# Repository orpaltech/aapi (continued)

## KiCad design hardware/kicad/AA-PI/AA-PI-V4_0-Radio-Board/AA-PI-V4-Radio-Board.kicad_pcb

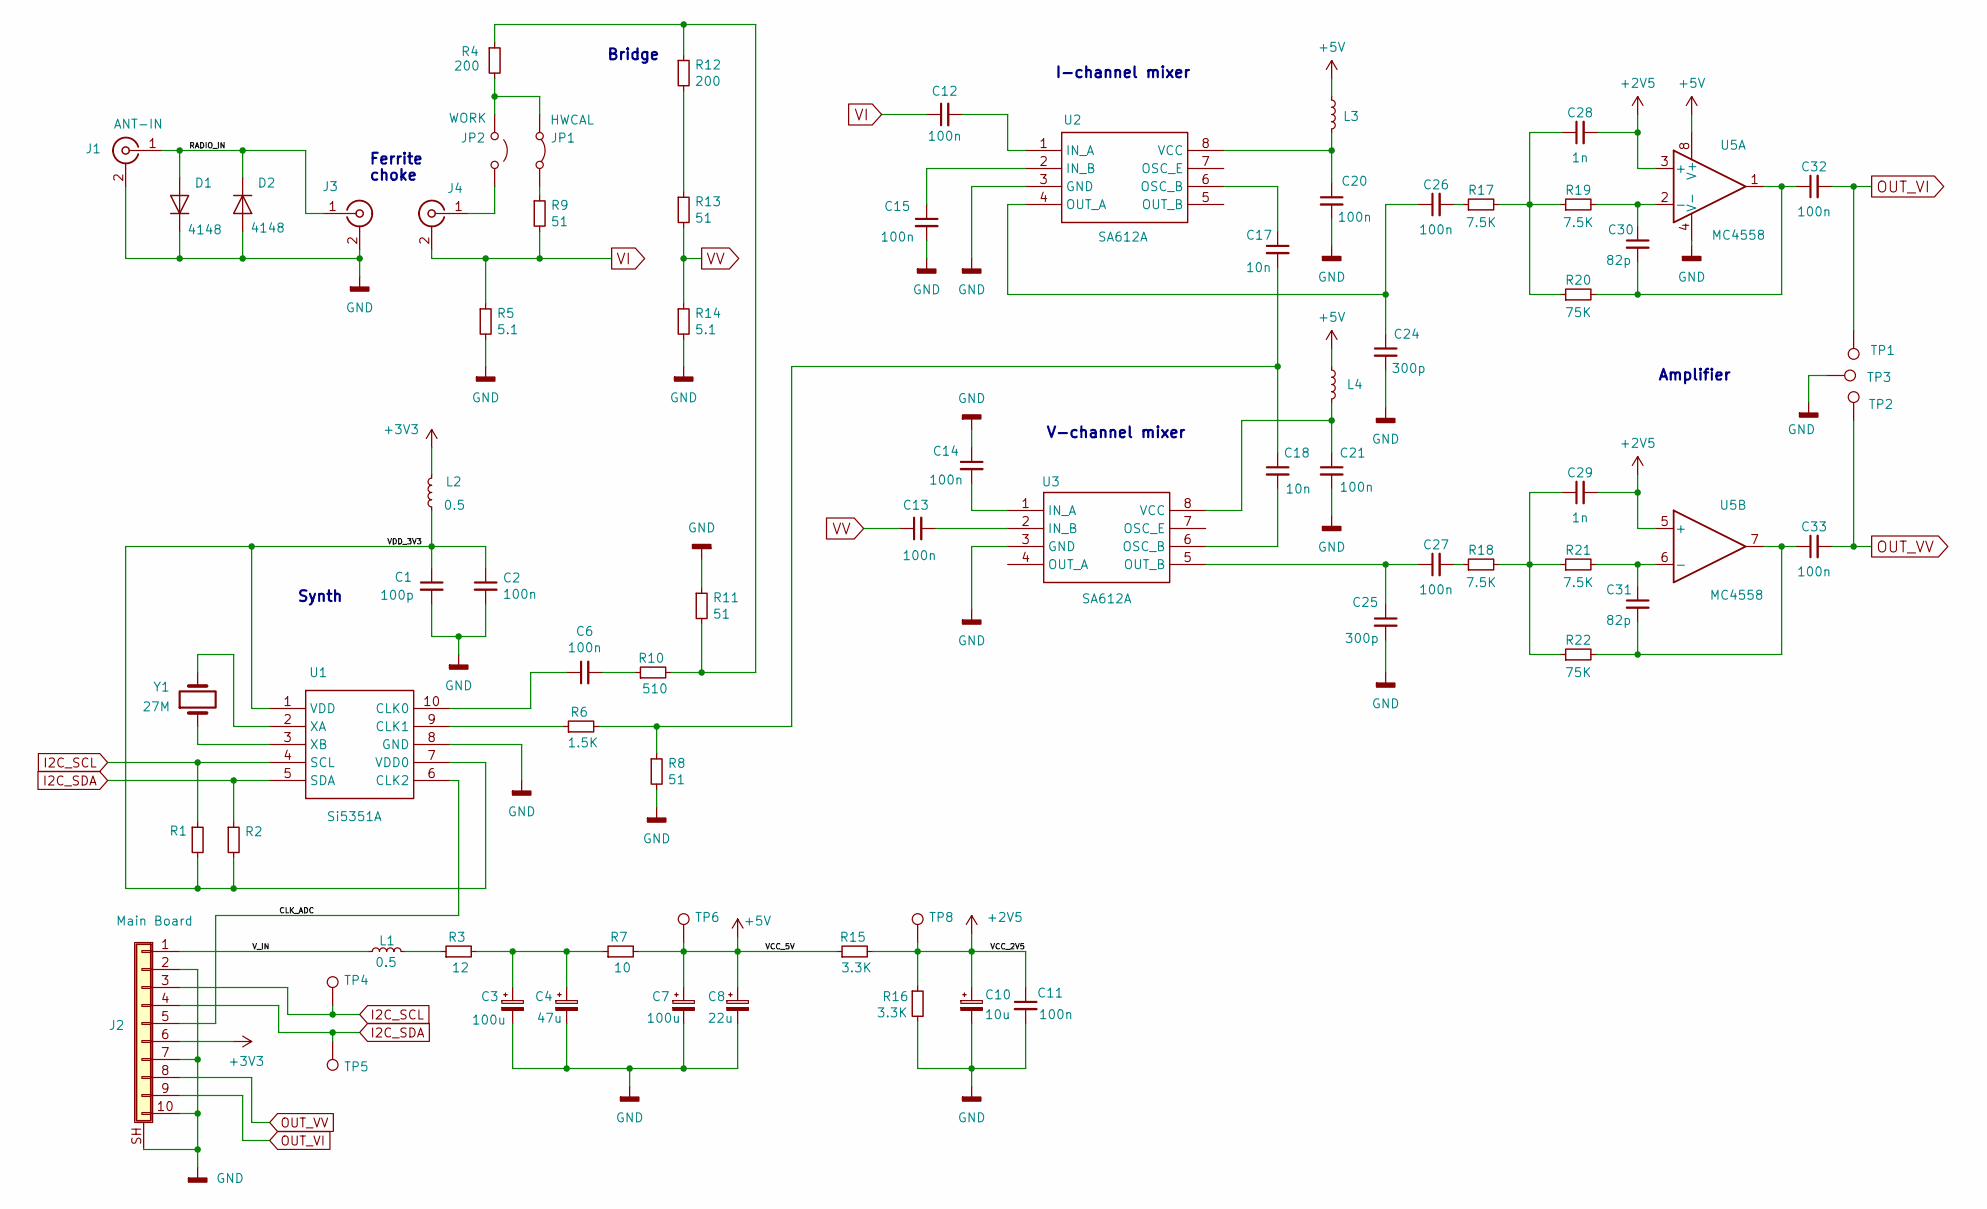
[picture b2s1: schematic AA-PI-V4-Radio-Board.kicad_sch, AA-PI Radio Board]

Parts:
C1: 100p; C_0805_2012Metric_Pad1.15x1.40mm_HandSolder
C2, C6, C11, C12, C13, C14, C15, C20, C21, C26, C27, C32, C33: 100n; C_0805_2012Metric_Pad1.15x1.40mm_HandSolder
C3, C7: 100u; CP_EIA-7343-31_Kemet-D
C4: 47u; CP_EIA-3528-21_Kemet-B
C8: 22u; CP_EIA-3528-21_Kemet-B
C10: 10u; CP_EIA-3528-21_Kemet-B
C17, C18: 10n; C_0805_2012Metric_Pad1.15x1.40mm_HandSolder
C24, C25: 300p; C_0805_2012Metric_Pad1.15x1.40mm_HandSolder
C28, C29: 1n; C_0805_2012Metric_Pad1.15x1.40mm_HandSolder
C30, C31: 82p; C_0805_2012Metric_Pad1.15x1.40mm_HandSolder
D1, D2: 4148; D_SOD-323_HandSoldering
J1: ANT-IN; SMA_Amphenol_901-144_Vertical
J2: Main Board; 1.25-AB-SMT-10pin-Vertical
J3, J4: INDUCT; MMCX_Molex_73415-1471_Vertical
JP1: HWCAL; PinHeader_1x02_P2.00mm_Vertical
JP2: WORK; PinHeader_1x02_P2.00mm_Vertical
L1, L2, L3, L4: 0.5; L_0805_2012Metric_Pad1.15x1.40mm_HandSolder
R1, R2: 10K; R_0805_2012Metric_Pad1.15x1.40mm_HandSolder
R3: 12; R_0805_2012Metric_Pad1.15x1.40mm_HandSolder
R4, R12: 200; R_0805_2012Metric_Pad1.15x1.40mm_HandSolder
R5, R14: 5.1; R_0805_2012Metric_Pad1.15x1.40mm_HandSolder
R6: 1.5K; R_0805_2012Metric_Pad1.15x1.40mm_HandSolder
R7: 10; R_0805_2012Metric_Pad1.15x1.40mm_HandSolder
R8, R9, R11, R13: 51; R_0805_2012Metric_Pad1.15x1.40mm_HandSolder
R10: 510; R_0805_2012Metric_Pad1.15x1.40mm_HandSolder
R15, R16: 3.3K; R_0805_2012Metric_Pad1.15x1.40mm_HandSolder
R17, R18, R19, R21: 7.5K; R_0805_2012Metric_Pad1.15x1.40mm_HandSolder
R20, R22: 75K; R_0805_2012Metric_Pad1.15x1.40mm_HandSolder
TP1, TP2, TP3, TP4, TP5, TP6, TP8: TestPoint; TestPoint_THTPad_D1.0mm_Drill0.5mm
U1: Si5351A; SOP50P490X110-10N; Manufacturer_Part_Number Si5351A-B-GT
U2, U3: SA612A; SOIC127P600X175-8N; Manufacturer_Part_Number SA612A
U5: MC4558; SOIC127P600X175-8N
Y1: 27M; Crystal_SMD_5032-2Pin_5.0x3.2mm

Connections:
+2V5: C10.1, C11.1, C28.2, C29.2, R15.2, R16.1, TP8.1, U5.3 (+), U5.5 (+)
+3V3: J2.6, L2.1
+5V: C7.1, C8.1, L3.1, L4.1, R7.2, R15.1, TP6.1, U5.8 (V+); also elsewhere on the board
/CLK_ADC: J2.5, U1.6 (CLK2)
/RADIO_IN: D1.2 (A), D2.1 (K), J1.1 (In), J3.1 (In)
/VDD_3V3: C1.1, C2.1, L2.2, R1.2, R2.2, U1.1 (VDD), U1.7 (VDD0)
/V_IN: J2.1, L1.1
GND: C1.2, C2.2, C3.2, C4.2, C7.2, C8.2, C10.2, C11.2, C14.1, C15.2, C20.2, C21.2, C24.2, C25.2, D1.1 (K), D2.2 (A), J1.2 (Ext), J2.2, J2.7, J2.10, J2.SH (Shield), J3.2 (Ext), R5.2, R8.2, R11.1, R14.2, R16.2, TP3.1, U1.8 (GND), U2.3 (GND), U3.3 (GND), U5.4 (V-); also elsewhere on the board
I2C_SCL: J2.3, R1.1, TP4.1, U1.4 (SCL)
I2C_SDA: J2.4, R2.1, TP5.1, U1.5 (SDA)
unnamed 10: C3.1, C4.1, R3.2, R7.1; also elsewhere on the board
unnamed: C6.2, R10.1
unnamed: C17.2, C18.1, R6.2, R8.1
unnamed: C26.2, R17.1
unnamed: C27.2, R18.1
unnamed: C28.1, R17.2, R19.1, R20.1
unnamed: C29.1, R18.2, R21.1, R22.1
unnamed: C30.2, C32.1, R20.2, U5.1
unnamed: C31.2, C33.1, R22.2, U5.7
unnamed: J4.1 (In), JP2.2 (B)
unnamed: JP1.1 (A), JP2.1 (A), R4.2
unnamed: JP1.2 (B), R9.1
unnamed: L1.2, R3.1
unnamed: R4.1, R10.2, R11.2, R12.1
unnamed: R12.2, R13.1
unnamed: C6.1, U1.10 (CLK0)
unnamed: R6.1, U1.9 (CLK1)
unnamed: U1.2 (XA), Y1.2
unnamed: U1.3 (XB), Y1.1
unnamed: C12.2, U2.1 (IN_A)
unnamed: C15.1, U2.2 (IN_B)
unnamed: C17.1, U2.6 (OSC_B)
unnamed: C24.1, C26.1, U2.4 (OUT_A)
unnamed: C20.1, L3.2, U2.8 (VCC)
unnamed: C14.2, U3.1 (IN_A)
unnamed: C13.2, U3.2 (IN_B)
unnamed: C18.2, U3.6 (OSC_B)
unnamed: C25.1, C27.1, U3.5 (OUT_B)
unnamed: C21.1, L4.2, U3.8 (VCC)
unnamed: C30.1, R19.2, U5.2 (-)
unnamed: C31.1, R21.2, U5.6 (-)
OUT_VI: C32.2, J2.9, TP1.1
OUT_VV: C33.2, J2.8, TP2.1
VI: C12.1, J4.2 (Ext), R5.1, R9.2
VV: C13.1, R13.2, R14.1

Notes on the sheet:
Ferrite
choke
V-channel mixer
Amplifier
Synth
I-channel mixer
Bridge

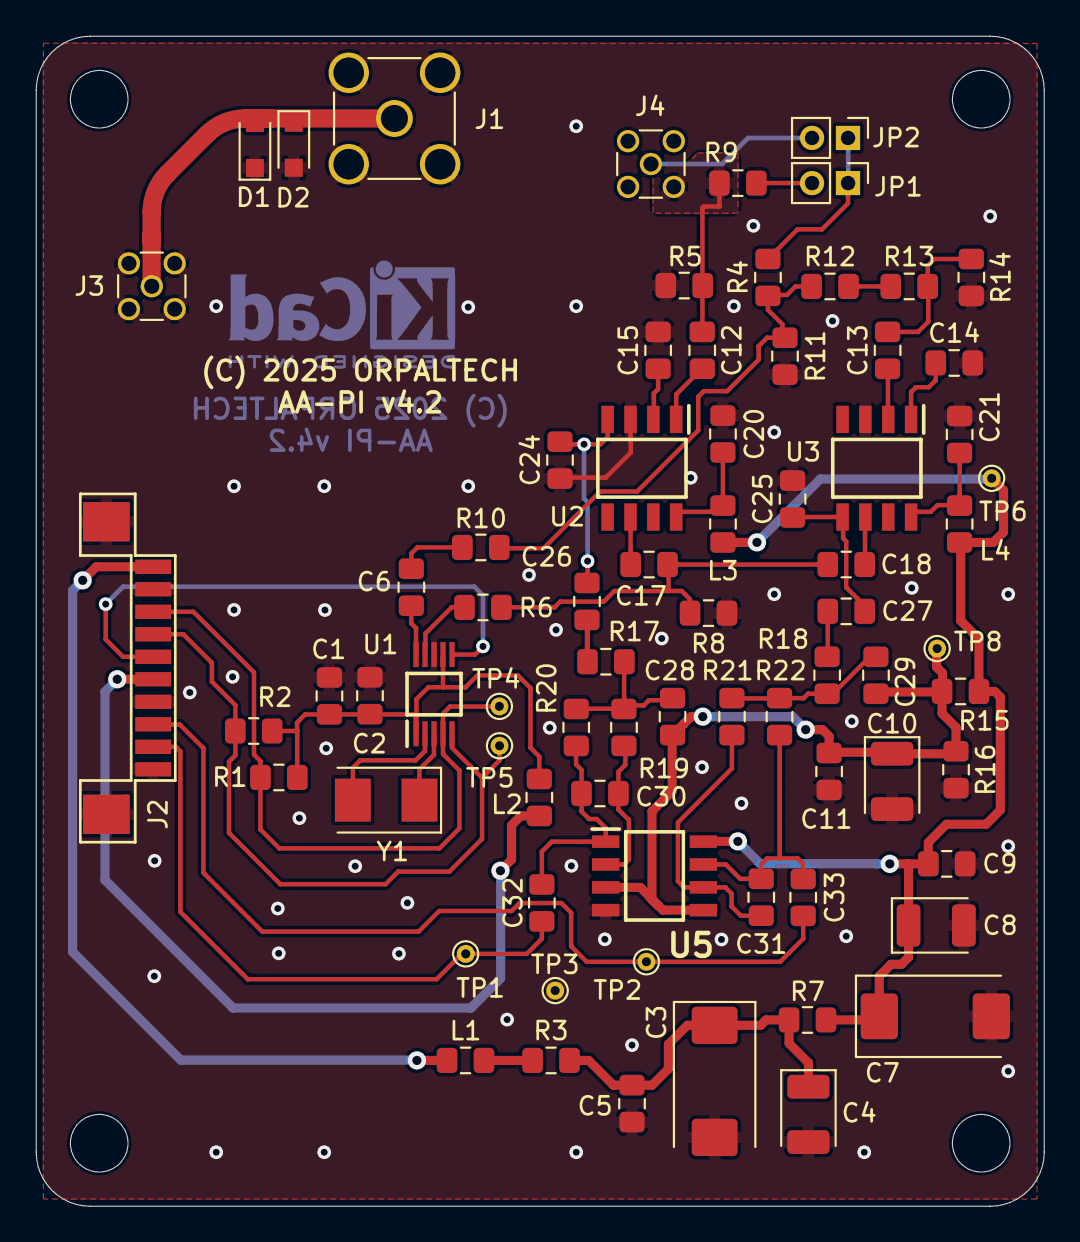
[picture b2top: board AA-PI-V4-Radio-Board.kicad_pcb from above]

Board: 2 copper layers, 56.0 x 65.0 mm, 79 parts (0 on the bottom side), 45 nets.

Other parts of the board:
C5, C9: 100n; C_0805_2012Metric_Pad1.15x1.40mm_HandSolder
MH1, MH2, MH3, MH4: MountingHole_3.2mm_M3_DIN965

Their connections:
+5V: C9.1; also elsewhere on the board
GND: C5.2, C9.2; also elsewhere on the board
unnamed 10: C5.1; also elsewhere on the board

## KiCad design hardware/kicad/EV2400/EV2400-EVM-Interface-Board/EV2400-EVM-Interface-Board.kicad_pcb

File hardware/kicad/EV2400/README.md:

This is my implementation of the Texas Instruments EV2400 Interface board. The board datasheet is located here http://www.ti.com/lit/ug/sluu446c/sluu446c.pdf

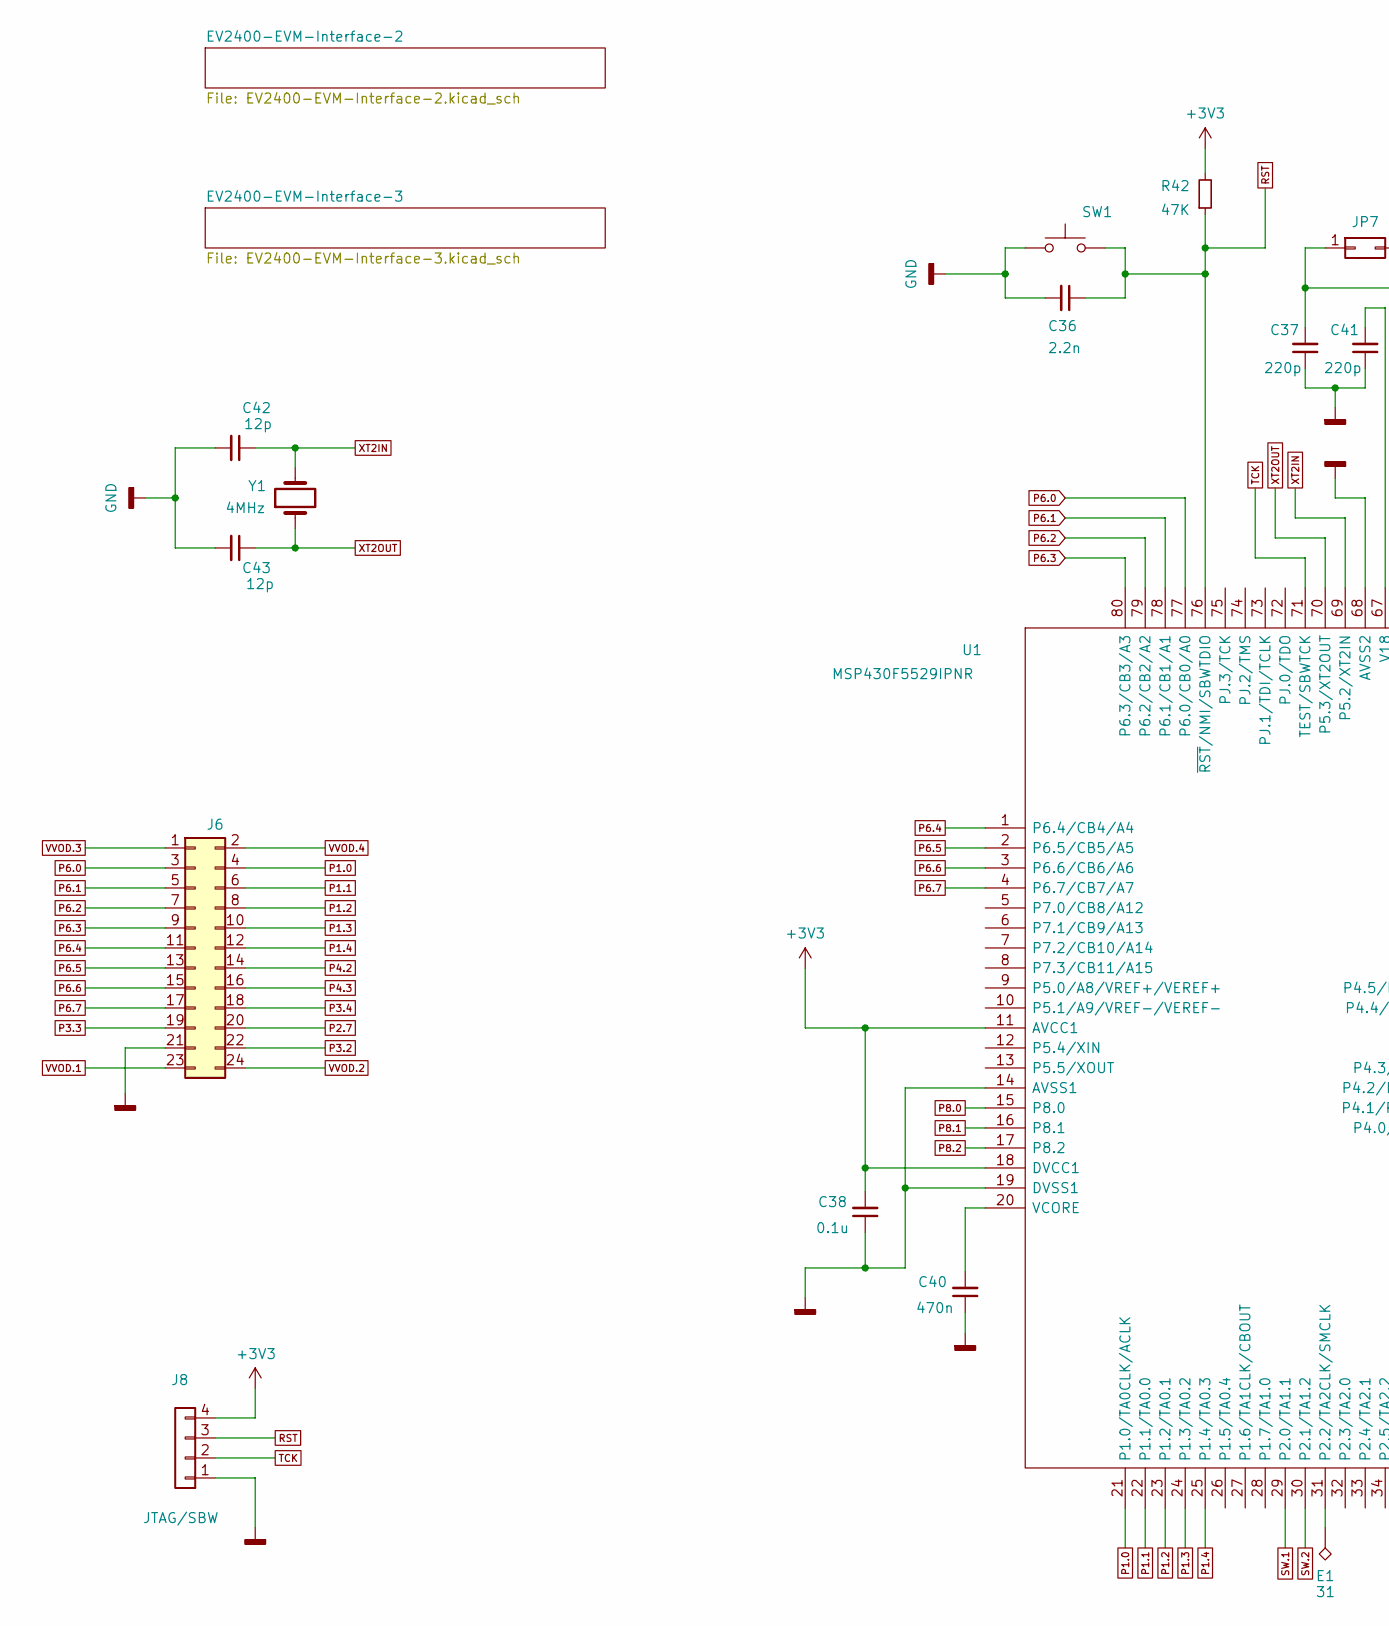
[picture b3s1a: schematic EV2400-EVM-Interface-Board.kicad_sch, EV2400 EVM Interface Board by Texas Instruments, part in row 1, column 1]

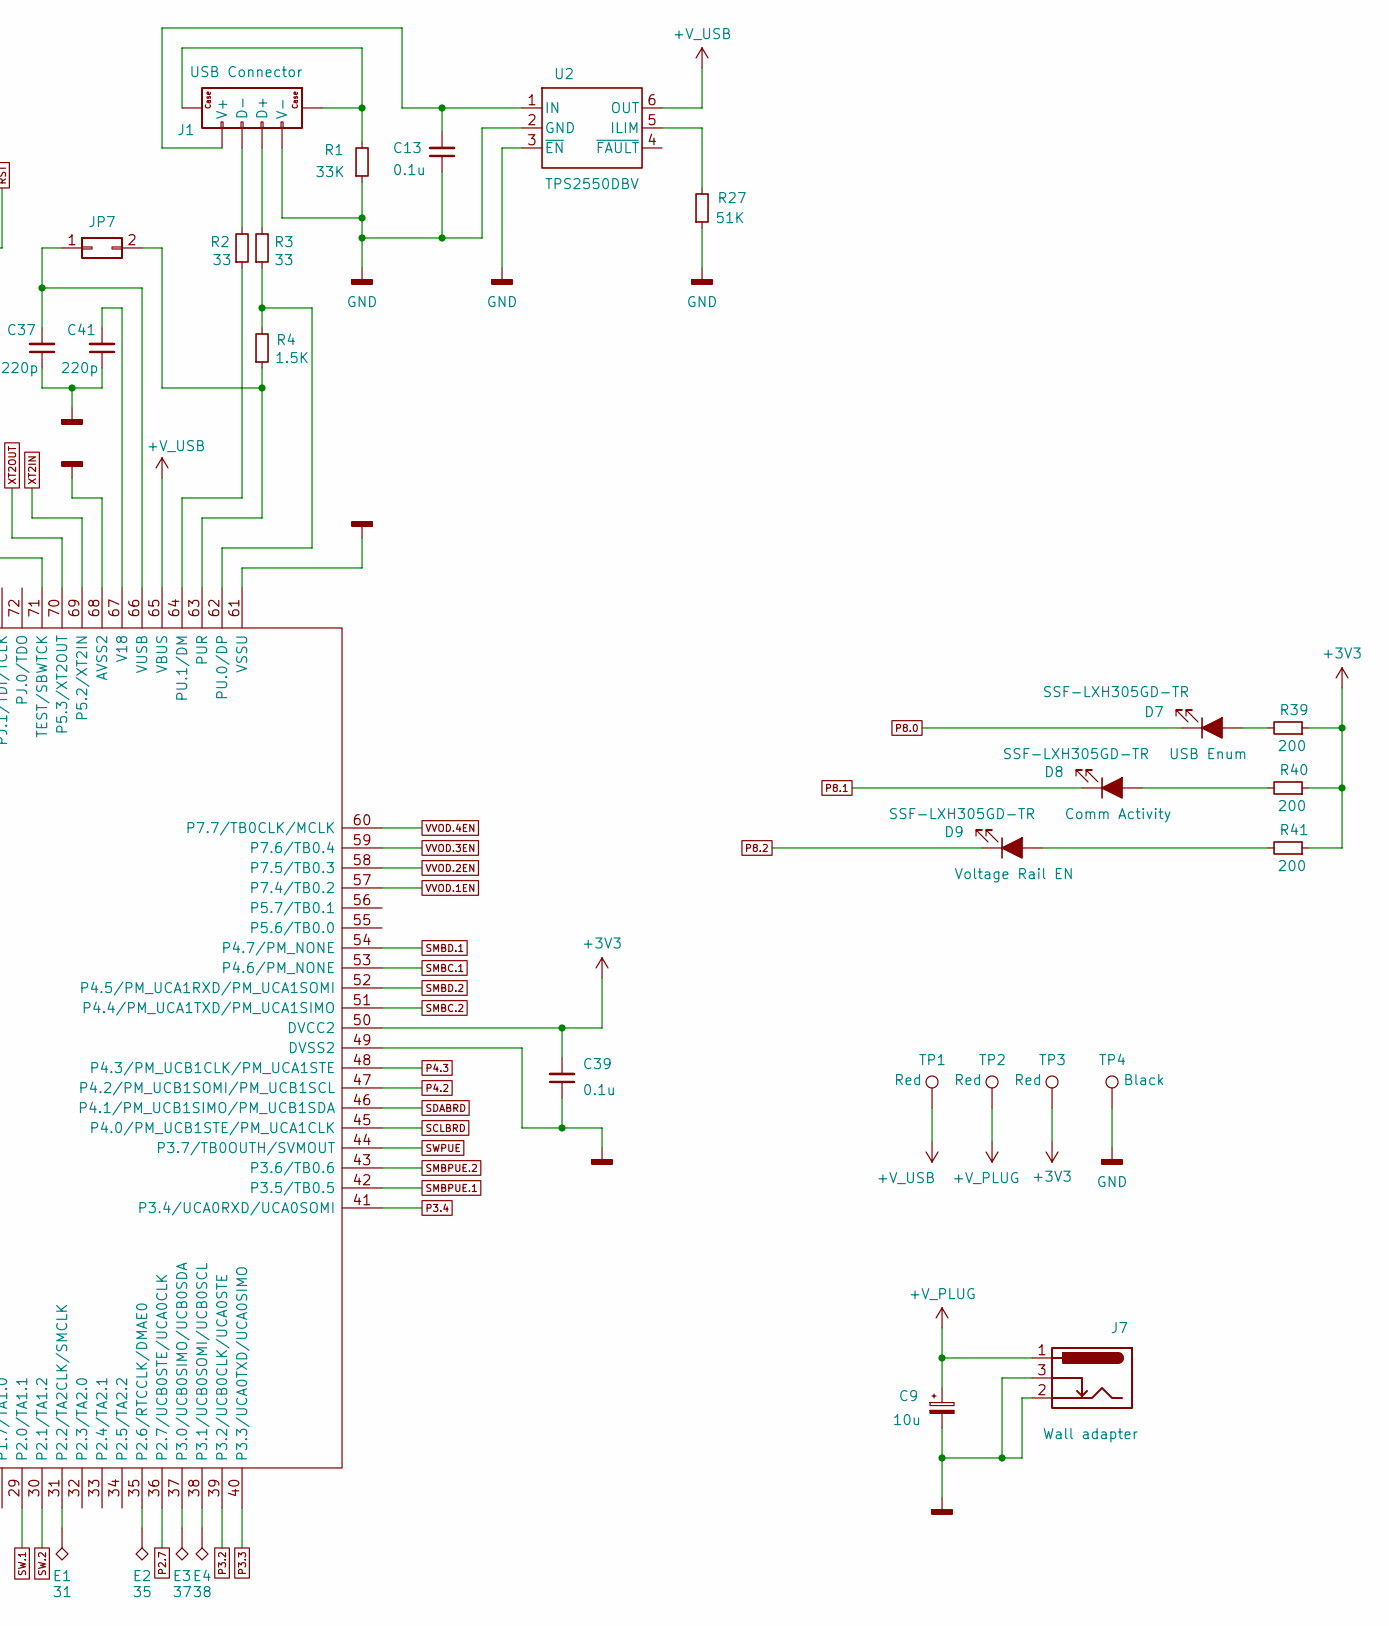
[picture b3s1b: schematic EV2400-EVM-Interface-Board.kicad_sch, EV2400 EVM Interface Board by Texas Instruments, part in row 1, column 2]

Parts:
C9: 10u; CP_EIA-3216-18_Kemet-A
C13, C38, C39: 0.1u; C_0603_1608Metric
C36: 2.2n; C_0603_1608Metric
C37, C41: 220p; C_0603_1608Metric
C40: 470n; C_0603_1608Metric
C42, C43: 12p; C_0603_1608Metric
D7, D8, D9: SSF-LXH305GD-TR; SSFLXH305GDTR
E1: 31; TestPoint_Pad_1.5x1.5mm
E2: 35; TestPoint_Pad_1.5x1.5mm
E3: 37; TestPoint_Pad_1.5x1.5mm
E4: 38; TestPoint_Pad_1.5x1.5mm
J1: USB Connector; USB_B_OST_USB-B1HSxx_Horizontal
J6: Conn_02x12_Odd_Even; PinHeader_2x12_P2.54mm_Horizontal
J7: Wall adapter; DC-050-SMD-Power-Jack
J8: JTAG/SBW; Molex_KK-254_AE-6410-04A_1x04_P2.54mm_Vertical
JP7: Conn_02x01; PinHeader_1x02_P2.54mm_Vertical
R1: 33K; R_0603_1608Metric
R2, R3: 33; R_0603_1608Metric
R4: 1.5K; R_0603_1608Metric
R27: 51K; R_0603_1608Metric
R39, R40, R41: 200; R_0603_1608Metric
R42: 47K; R_0603_1608Metric
SW1: EVQPSD02K
TP1, TP2, TP3, TP4: TestPoint; TestPoint_THTPad_D2.0mm_Drill1.0mm
U1: MSP430F5529IPNR; QFP50P1400X1400X160-80N; Manufacturer_Part_Number MSP430F5529IPNR
U2: TPS2550DBV; SOT95P280X145-6N; Manufacturer_Part_Number TPS2550DBV
Y1: 4MHz; Crystal_SMD_HC49-SD

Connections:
+3V3: C38.2, C39.2, J8.4, R39.1, R40.1, R41.1, R42.2, TP3.1, U1.11 (AVCC1), U1.18 (DVCC1), U1.50 (DVCC2); also elsewhere on the board
+V_PLUG: C9.1, J7.1, TP2.1; also elsewhere on the board
+V_USB: TP1.1, U1.65 (VBUS), U2.6 (OUT); also elsewhere on the board
GND: C9.2, C13.1, C36.2, C37.1, C38.1, C39.1, C40.1, C41.1, C42.2, C43.2, J1.4 (V-), J6.21, J7.2, J7.3, J8.1, R1.1, R27.1, SW1.1, TP4.1, U1.14 (AVSS1), U1.19 (DVSS1), U1.49 (DVSS2), U1.61 (VSSU), U1.68 (AVSS2), U2.2 (GND), U2.3 (~EN); also elsewhere on the board
unnamed: D7.2 (A), R39.2
unnamed: D8.2 (A), R40.2
unnamed: D9.2 (A), R41.2
unnamed: J1.3 (D+), R3.2
unnamed: J1.2 (D-), R2.2
unnamed: J1.5, R1.2
unnamed: C13.2, J1.1 (V+), U2.1 (IN)
unnamed: C37.2, JP7.1, U1.66 (VUSB)
unnamed: JP7.2, R4.1, U1.63 (PUR)
unnamed: E1.1, U1.31 (P2.2/TA2CLK/SMCLK)
unnamed: E2.1, U1.35 (P2.6/RTCCLK/DMAE0)
unnamed: E3.1, U1.37 (P3.0/UCB0SIMO/UCB0SDA)
unnamed: E4.1, U1.38 (P3.1/UCB0SOMI/UCB0SCL)
unnamed: R3.1, R4.2, U1.62 (PU.0/DP)
unnamed: R2.1, U1.64 (PU.1/DM)
unnamed: C41.2, U1.67 (V18)
unnamed: C40.2, U1.20 (VCORE)
unnamed: R27.2, U2.5 (ILIM)
P1.0: J6.4, U1.21 (P1.0/TA0CLK/ACLK)
P1.1: J6.6, U1.22 (P1.1/TA0.0)
P1.2: J6.8, U1.23 (P1.2/TA0.1)
P1.3: J6.10, U1.24 (P1.3/TA0.2)
P1.4: J6.12, U1.25 (P1.4/TA0.3)
P2.7: J6.20, U1.36 (P2.7/UCB0STE/UCA0CLK)
P3.2: J6.22, U1.39 (P3.2/UCB0CLK/UCA0STE)
P3.3: J6.19, U1.40 (P3.3/UCA0TXD/UCA0SIMO)
P3.4: J6.18, U1.41 (P3.4/UCA0RXD/UCA0SOMI)
P4.2: J6.14, U1.47 (P4.2/PM_UCB1SOMI/PM_UCB1SCL)
P4.3: J6.16, U1.48 (P4.3/PM_UCB1CLK/PM_UCA1STE)
P6.0: J6.3, U1.77 (P6.0/CB0/A0)
P6.1: J6.5, U1.78 (P6.1/CB1/A1)
P6.2: J6.7, U1.79 (P6.2/CB2/A2)
P6.3: J6.9, U1.80 (P6.3/CB3/A3)
P6.4: J6.11, U1.1 (P6.4/CB4/A4)
P6.5: J6.13, U1.2 (P6.5/CB5/A5)
P6.6: J6.15, U1.3 (P6.6/CB6/A6)
P6.7: J6.17, U1.4 (P6.7/CB7/A7)
P8.0: D7.1 (K), U1.15 (P8.0)
P8.1: D8.1 (K), U1.16 (P8.1)
P8.2: D9.1 (K), U1.17 (P8.2)
RST: C36.1, J8.3, R42.1, SW1.2, U1.76 (~RST/NMI/SBWTDIO)
SCLBRD: U1.45 (P4.0/PM_UCB1STE/PM_UCA1CLK); also elsewhere on the board
SDABRD: U1.46 (P4.1/PM_UCB1SIMO/PM_UCB1SDA); also elsewhere on the board
SMBC.1: U1.53 (P4.6/PM_NONE); also elsewhere on the board
SMBC.2: U1.51 (P4.4/PM_UCA1TXD/PM_UCA1SIMO); also elsewhere on the board
SMBD.1: U1.54 (P4.7/PM_NONE); also elsewhere on the board
SMBD.2: U1.52 (P4.5/PM_UCA1RXD/PM_UCA1SOMI); also elsewhere on the board
SMBPUE.1: U1.42 (P3.5/TB0.5); also elsewhere on the board
SMBPUE.2: U1.43 (P3.6/TB0.6); also elsewhere on the board
SW.1: U1.29 (P2.0/TA1.1); also elsewhere on the board
SW.2: U1.30 (P2.1/TA1.2); also elsewhere on the board
SWPUE: U1.44 (P3.7/TB0OUTH/SVMOUT); also elsewhere on the board
TCK: J8.2, U1.71 (TEST/SBWTCK)
VVOD.1: J6.23; also elsewhere on the board
VVOD.1EN: U1.57 (P7.4/TB0.2); also elsewhere on the board
VVOD.2: J6.24; also elsewhere on the board
VVOD.2EN: U1.58 (P7.5/TB0.3); also elsewhere on the board
VVOD.3: J6.1; also elsewhere on the board
VVOD.3EN: U1.59 (P7.6/TB0.4); also elsewhere on the board
VVOD.4: J6.2; also elsewhere on the board
VVOD.4EN: U1.60 (P7.7/TB0CLK/MCLK); also elsewhere on the board
XT2IN: C42.1, U1.69 (P5.2/XT2IN), Y1.2
XT2OUT: C43.1, U1.70 (P5.3/XT2OUT), Y1.1

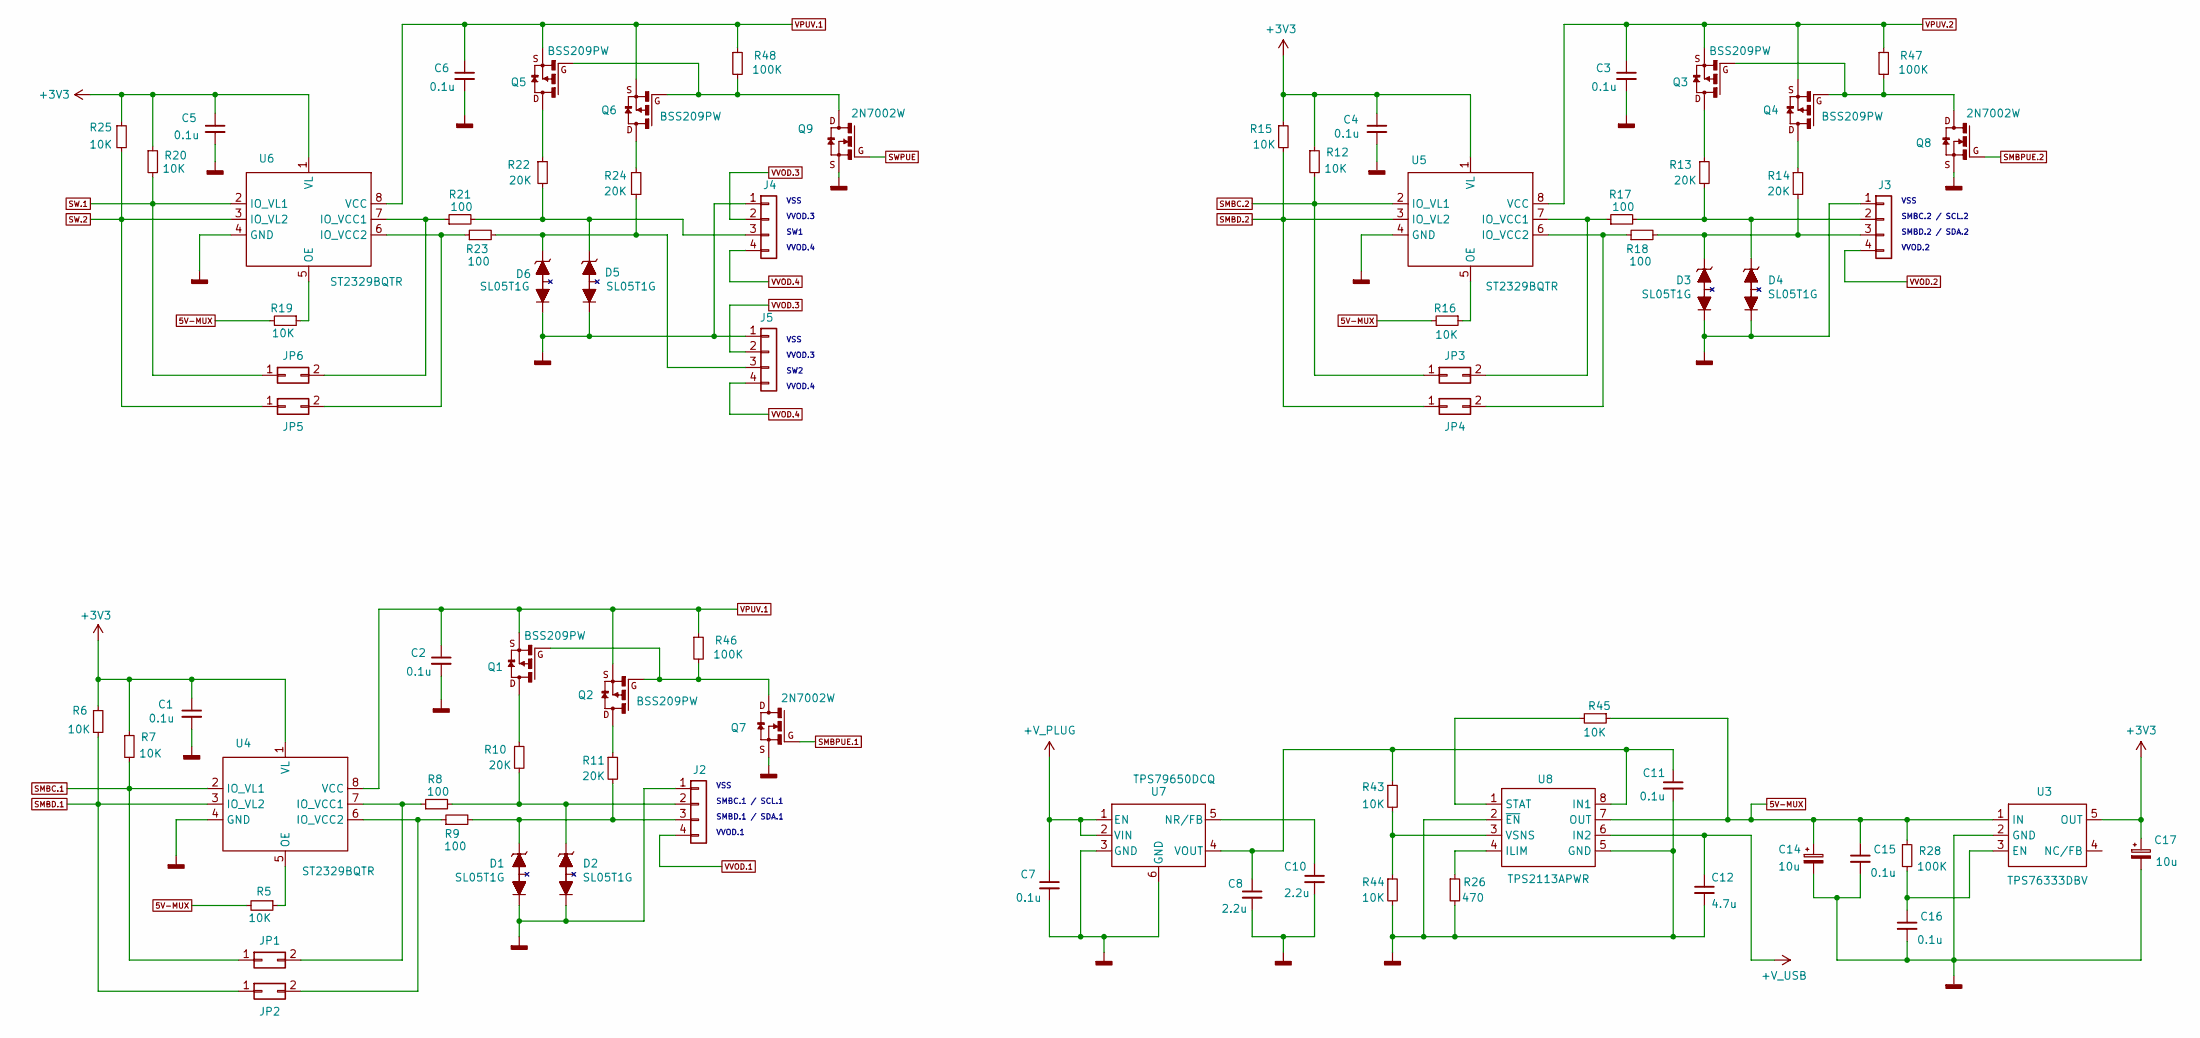
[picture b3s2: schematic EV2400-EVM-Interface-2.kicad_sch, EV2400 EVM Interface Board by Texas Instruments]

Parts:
C1, C2, C3, C4, C5, C6, C7, C11, C15, C16: 0.1u; C_0603_1608Metric
C8, C10: 2.2u; C_0805_2012Metric
C12: 4.7u; C_0805_2012Metric
C14, C17: 10u; CP_EIA-3216-18_Kemet-A
D1, D2, D3, D4, D5, D6: SL05T1G; SOT96P237X111-3N; Manufacturer_Part_Number SL05T1G
J2, J3, J4, J5: Conn_01x04; Molex_22053041
JP1, JP2, JP3, JP4, JP5, JP6: Conn_02x01; PinHeader_1x02_P2.54mm_Vertical
Q1, Q2, Q3, Q4, Q5, Q6: BSS209PW; SOT65P210X100-3N
Q7, Q8, Q9: 2N7002W; SOT65P220X100-3N
R5, R6, R7, R12, R15, R16, R19, R20, R25, R43, R44, R45: 10K; R_0603_1608Metric
R8, R9, R17, R18, R21, R23: 100; R_0603_1608Metric
R10, R11, R13, R14, R22, R24: 20K; R_0603_1608Metric
R26: 470; R_0603_1608Metric
R28, R46, R47, R48: 100K; R_0603_1608Metric
U3: TPS76333DBV; SOT95P280X145-5N; Manufacturer_Part_Number TPS76333DBVT
U4, U5, U6: ST2329BQTR; QFN40P120X140X55-8N; Manufacturer_Part_Number ST2329BQTR
U7: TPS79650DCQ; SOT127P706X180-6N; Manufacturer_Part_Number TPS79650DCQ
U8: TPS2113APWR; SOP65P640X120-8N; Manufacturer_Part_Number TPS2113APWR

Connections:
5V-MUX: C14.1, C15.1, R5.2, R16.2, R19.2, R28.1, R45.1, U3.1 (IN), U8.7 (OUT); also elsewhere on the board
+3V3: C1.1, C4.1, C5.1, C17.1, R6.1, R7.1, R12.1, R15.1, R20.1, R25.1, U3.5 (OUT), U4.1 (VL), U5.1 (VL), U6.1 (VL); also elsewhere on the board
+V_PLUG: C7.1, U7.1 (EN), U7.2 (VIN); also elsewhere on the board
+V_USB: C12.1, U8.6 (IN2); also elsewhere on the board
GND: C1.2, C2.2, C3.2, C4.2, C5.2, C6.2, C7.2, C8.2, C10.2, C11.2, C12.2, C14.2, C15.2, C16.2, C17.2, D1.2, D2.2, D3.2, D4.2, D5.2, D6.2, J2.1, J3.1, J4.1, J5.1, Q7.2 (S), Q8.2 (S), Q9.2 (S), R26.2, R44.2, U3.2 (GND), U4.4 (GND), U5.4 (GND), U6.4 (GND), U7.3 (GND), U7.6 (GND), U8.2 (~EN), U8.5 (GND); also elsewhere on the board
unnamed: D2.1, J2.2, R8.2, R10.2
unnamed: D1.1, J2.3, R9.2, R11.2
unnamed: D4.1, J3.2, R13.2, R17.2
unnamed: D3.1, J3.3, R14.2, R18.2
unnamed: D5.1, J4.3, R21.2, R22.2
unnamed: D6.1, J5.3, R23.2, R24.2
unnamed: JP1.2, R8.1, U4.7 (IO_VCC1)
unnamed: JP2.2, R9.1, U4.6 (IO_VCC2)
unnamed: JP3.2, R17.1, U5.7 (IO_VCC1)
unnamed: JP4.2, R18.1, U5.6 (IO_VCC2)
unnamed: JP5.2, R23.1, U6.6 (IO_VCC2)
unnamed: JP6.2, R21.1, U6.7 (IO_VCC1)
unnamed: Q1.3 (D), R10.1
unnamed: Q1.1 (G), Q2.1 (G), Q7.3 (D), R46.2
unnamed: Q2.3 (D), R11.1
unnamed: Q3.3 (D), R13.1
unnamed: Q3.1 (G), Q4.1 (G), Q8.3 (D), R47.2
unnamed: Q4.3 (D), R14.1
unnamed: Q5.3 (D), R22.1
unnamed: Q5.1 (G), Q6.1 (G), Q9.3 (D), R48.2
unnamed: Q6.3 (D), R24.1
unnamed: C16.1, R28.2, U3.3 (EN)
unnamed: R5.1, U4.5 (OE)
unnamed: R16.1, U5.5 (OE)
unnamed: R19.1, U6.5 (OE)
unnamed: C10.1, U7.5 (NR/FB)
unnamed: C8.1, C11.1, R43.1, U7.4 (VOUT), U8.8 (IN1)
unnamed: R26.1, U8.4 (ILIM)
unnamed: R45.2, U8.1 (STAT)
unnamed: R43.2, R44.1, U8.3 (VSNS)
SMBC.1: JP1.1, R7.2, U4.2 (IO_VL1); also elsewhere on the board
SMBC.2: JP3.1, R12.2, U5.2 (IO_VL1); also elsewhere on the board
SMBD.1: JP2.1, R6.2, U4.3 (IO_VL2); also elsewhere on the board
SMBD.2: JP4.1, R15.2, U5.3 (IO_VL2); also elsewhere on the board
SMBPUE.1: Q7.1 (G); also elsewhere on the board
SMBPUE.2: Q8.1 (G); also elsewhere on the board
SW.1: JP6.1, R20.2, U6.2 (IO_VL1); also elsewhere on the board
SW.2: JP5.1, R25.2, U6.3 (IO_VL2); also elsewhere on the board
SWPUE: Q9.1 (G); also elsewhere on the board
VPUV.1: C2.1, C6.1, Q1.2 (S), Q2.2 (S), Q5.2 (S), Q6.2 (S), R46.1, R48.1, U4.8 (VCC), U6.8 (VCC); also elsewhere on the board
VPUV.2: C3.1, Q3.2 (S), Q4.2 (S), R47.1, U5.8 (VCC); also elsewhere on the board
VVOD.1: J2.4; also elsewhere on the board
VVOD.2: J3.4; also elsewhere on the board
VVOD.3: J4.2, J5.2; also elsewhere on the board
VVOD.4: J4.4, J5.4; also elsewhere on the board

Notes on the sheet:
VVOD.4
VSS
SW2
SMBC.1 / SCL.1
VVOD.3
VVOD.1
SMBC.2 / SCL.2
SMBD.2 / SDA.2
VVOD.2
SMBD.1 / SDA.1
SW1

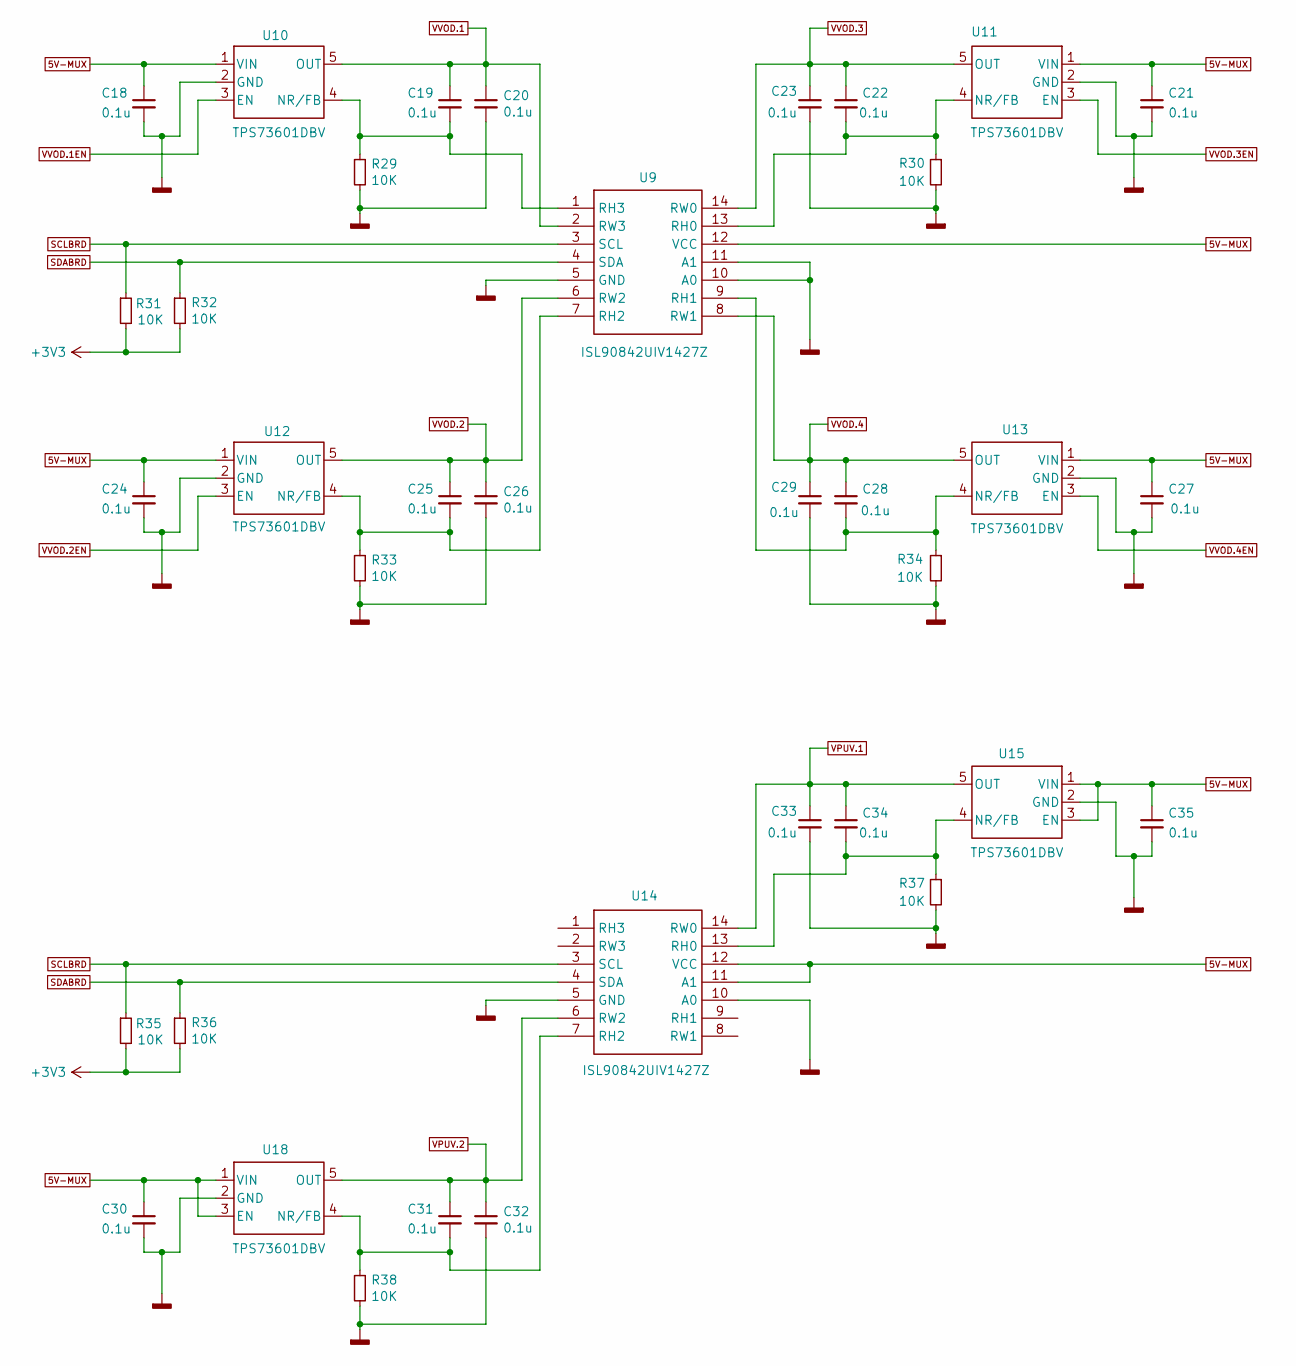
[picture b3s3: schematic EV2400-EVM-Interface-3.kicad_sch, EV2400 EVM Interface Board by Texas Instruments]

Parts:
C18, C19, C20, C21, C22, C23, C24, C25, C26, C27, C28, C29, C30, C31, C32, C33, C34, C35: 0.1u; C_0603_1608Metric
R29, R30, R31, R32, R33, R34, R35, R36, R37, R38: 10K; R_0603_1608Metric
U9, U14: ISL90842UIV1427Z; SOP65P640X105-14N; Manufacturer_Part_Number ISL90842UIV1427Z
U10, U11, U12, U13, U15, U18: TPS73601DBV; SOT95P280X145-5N; Manufacturer_Part_Number TPS73601DBV

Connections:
5V-MUX: C18.1, C21.1, C24.1, C27.1, C30.1, C35.1, U9.12 (VCC), U10.1 (VIN), U11.1 (VIN), U12.1 (VIN), U13.1 (VIN), U14.11 (A1), U14.12 (VCC), U15.1 (VIN), U15.3 (EN), U18.1 (VIN), U18.3 (EN); also elsewhere on the board
+3V3: R31.2, R32.2, R35.2, R36.2; also elsewhere on the board
GND: C18.2, C20.2, C21.2, C23.2, C24.2, C26.2, C27.2, C29.2, C30.2, C32.2, C33.2, C35.2, R29.2, R30.2, R33.2, R34.2, R37.2, R38.2, U9.5 (GND), U9.10 (A0), U9.11 (A1), U10.2 (GND), U11.2 (GND), U12.2 (GND), U13.2 (GND), U14.5 (GND), U14.10 (A0), U15.2 (GND), U18.2 (GND); also elsewhere on the board
unnamed: C19.2, R29.1, U9.1 (RH3), U10.4 (NR/FB)
unnamed: C22.2, R30.1, U9.13 (RH0), U11.4 (NR/FB)
unnamed: C25.2, R33.1, U9.7 (RH2), U12.4 (NR/FB)
unnamed: C28.2, R34.1, U9.9 (RH1), U13.4 (NR/FB)
unnamed: C34.2, R37.1, U14.13 (RH0), U15.4 (NR/FB)
unnamed: C31.2, R38.1, U14.7 (RH2), U18.4 (NR/FB)
SCLBRD: R31.1, R35.1, U9.3 (SCL), U14.3 (SCL); also elsewhere on the board
SDABRD: R32.1, R36.1, U9.4 (SDA), U14.4 (SDA); also elsewhere on the board
VPUV.1: C33.1, C34.1, U14.14 (RW0), U15.5 (OUT); also elsewhere on the board
VPUV.2: C31.1, C32.1, U14.6 (RW2), U18.5 (OUT); also elsewhere on the board
VVOD.1: C19.1, C20.1, U9.2 (RW3), U10.5 (OUT); also elsewhere on the board
VVOD.1EN: U10.3 (EN); also elsewhere on the board
VVOD.2: C25.1, C26.1, U9.6 (RW2), U12.5 (OUT); also elsewhere on the board
VVOD.2EN: U12.3 (EN); also elsewhere on the board
VVOD.3: C22.1, C23.1, U9.14 (RW0), U11.5 (OUT); also elsewhere on the board
VVOD.3EN: U11.3 (EN); also elsewhere on the board
VVOD.4: C28.1, C29.1, U9.8 (RW1), U13.5 (OUT); also elsewhere on the board
VVOD.4EN: U13.3 (EN); also elsewhere on the board
